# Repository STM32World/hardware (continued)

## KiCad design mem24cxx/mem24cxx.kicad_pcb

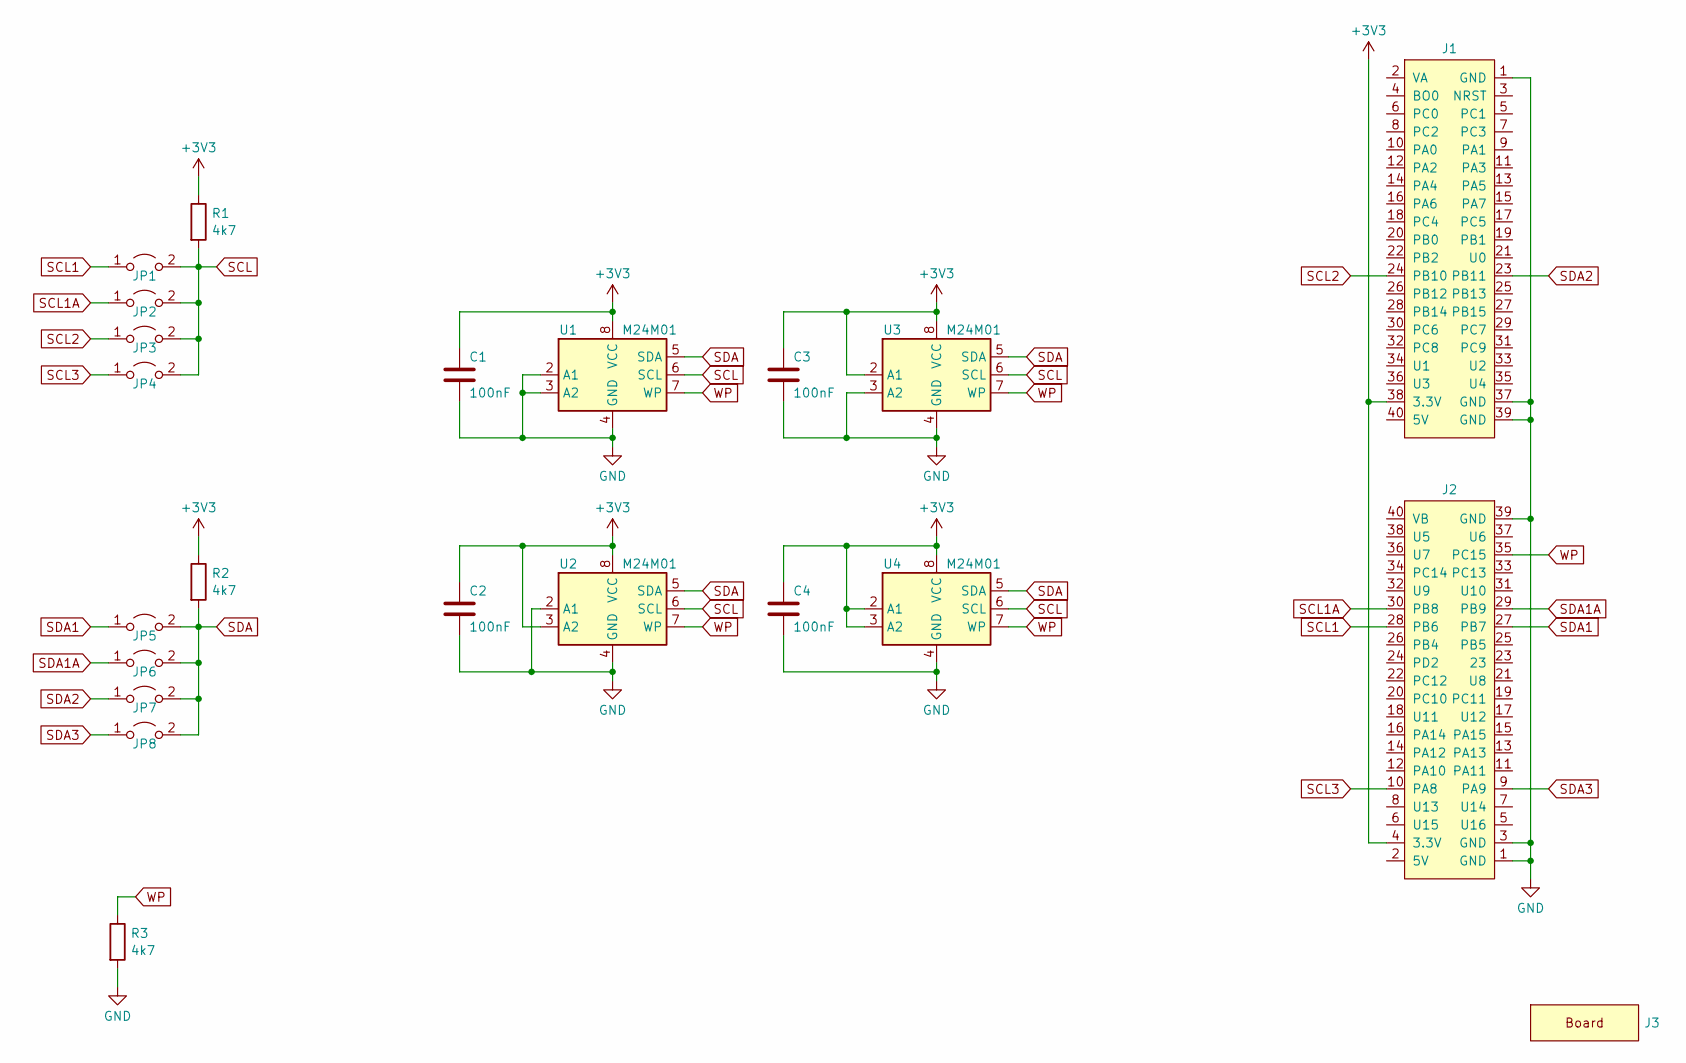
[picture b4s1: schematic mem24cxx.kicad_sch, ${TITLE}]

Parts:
C1, C2, C3, C4: 100nF; C_0603_1608Metric; LCSC C14663
J1: STM32WORLD_CONNECTOR_1; PinSocket_2x20_P2.54mm_Vertical_Stackable; LCSC C35165
J2: STM32WORLD_CONNECTOR_2; PinSocket_2x20_P2.54mm_Vertical_Stackable; LCSC C35165
J3: STM32WORLD_BOARD
JP1, JP2, JP3, JP4, JP5, JP6, JP7, JP8: SolderJumper-2_P1.3mm_Open_TrianglePad1.0x1.5mm
R1, R2, R3: 4k7; R_0603_1608Metric; LCSC C23162
U1, U2, U3, U4: M24M01; SOIC-8_3.9x4.9mm_P1.27mm; LCSC C79990

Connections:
+3V3: C1.1, C2.1, C3.1, C4.1, J1.38 (3.3V), J2.4 (3.3V), R1.1, R2.1, U1.8 (VCC), U2.3 (A2), U2.8 (VCC), U3.2 (A1), U3.8 (VCC), U4.2 (A1), U4.3 (A2), U4.8 (VCC)
GND: C1.2, C2.2, C3.2, C4.2, J1.1 (GND), J1.37 (GND), J1.39 (GND), J2.1 (GND), J2.3 (GND), J2.39 (GND), R3.2, U1.2 (A1), U1.3 (A2), U1.4 (GND), U2.2 (A1), U2.4 (GND), U3.3 (A2), U3.4 (GND), U4.4 (GND)
SCL: JP1.2 (B), JP2.2 (B), JP3.2 (B), JP4.2 (B), R1.2, U1.6 (SCL), U2.6 (SCL), U3.6 (SCL), U4.6 (SCL)
SCL1: J2.28 (PB6), JP1.1 (A)
SCL1A: J2.30 (PB8), JP2.1 (A)
SCL2: J1.24 (PB10), JP3.1 (A)
SCL3: J2.10 (PA8), JP4.1 (A)
SDA: JP5.2 (B), JP6.2 (B), JP7.2 (B), JP8.2 (B), R2.2, U1.5 (SDA), U2.5 (SDA), U3.5 (SDA), U4.5 (SDA)
SDA1: J2.27 (PB7), JP5.1 (A)
SDA1A: J2.29 (PB9), JP6.1 (A)
SDA2: J1.23 (PB11), JP7.1 (A)
SDA3: J2.9 (PA9), JP8.1 (A)
WP: J2.35 (PC15), R3.1, U1.7 (WP), U2.7 (WP), U3.7 (WP), U4.7 (WP)

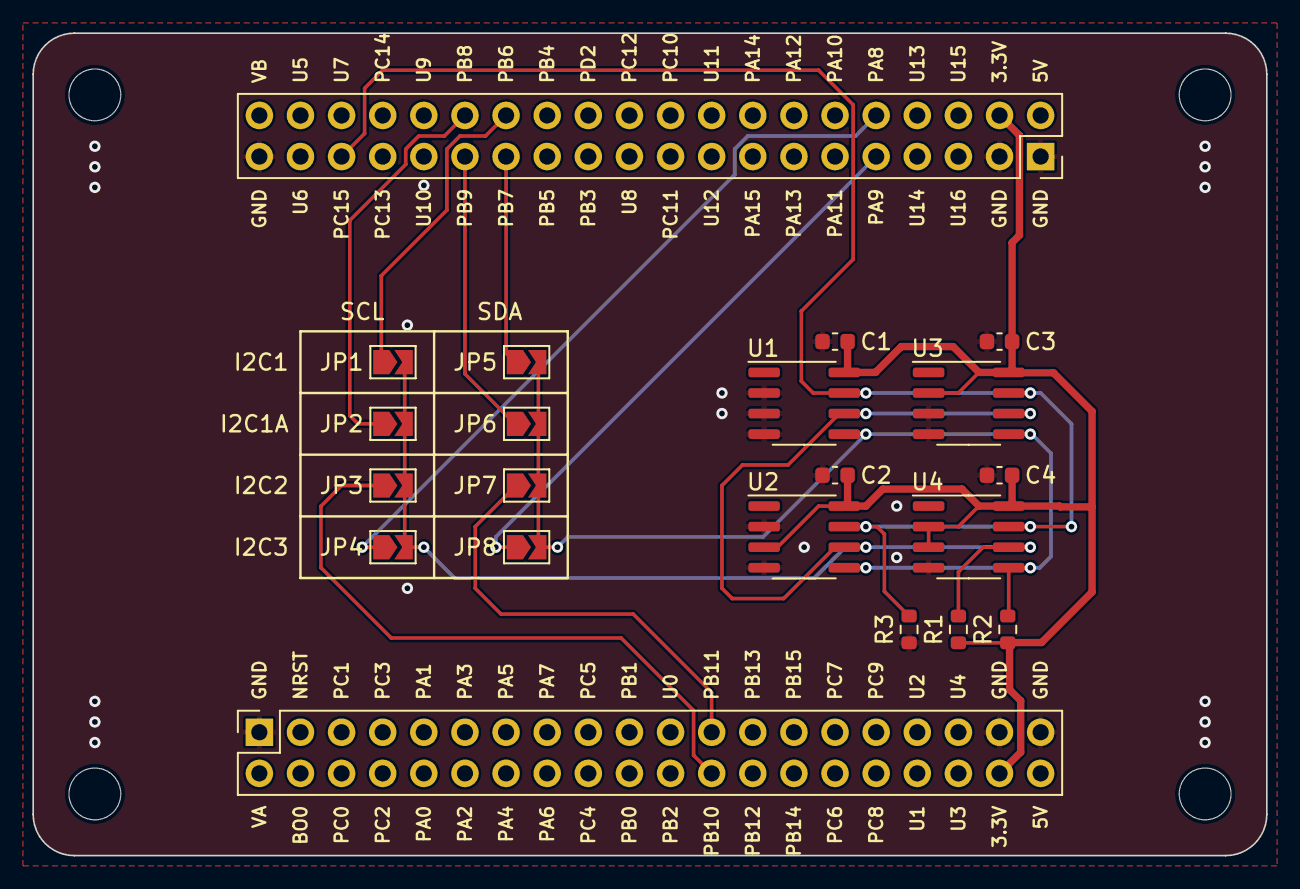
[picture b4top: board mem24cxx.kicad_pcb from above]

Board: 2 copper layers, 76.2 x 50.8 mm, 22 parts (0 on the bottom side), 13 nets.

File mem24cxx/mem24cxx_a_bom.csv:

Comment,Designator,Footprint,LCSC
"100nF","C1,C2,C3,C4","Capacitor_SMD:C_0603_1608Metric","C14663"
"STM32WORLD_CONNECTOR_1","J1","stm32world:PinSocket_2x20_P2.54mm_Vertical_Stackable","C35165"
"STM32WORLD_CONNECTOR_2","J2","stm32world:PinSocket_2x20_P2.54mm_Vertical_Stackable","C35165"
"STM32WORLD_BOARD","J3","stm32world:STM32WORLD_BOARD"
"~","JP1,JP2,JP3,JP4,JP5,JP6,JP7,JP8","Jumper:SolderJumper-2_P1.3mm_Open_TrianglePad1.0x1.5mm"
"4k7","R1,R2,R3","Resistor_SMD:R_0603_1608Metric","C23162"
"M24M01","U1,U2,U3,U4","Package_SO:SOIC-8_3.9x4.9mm_P1.27mm","C79990"

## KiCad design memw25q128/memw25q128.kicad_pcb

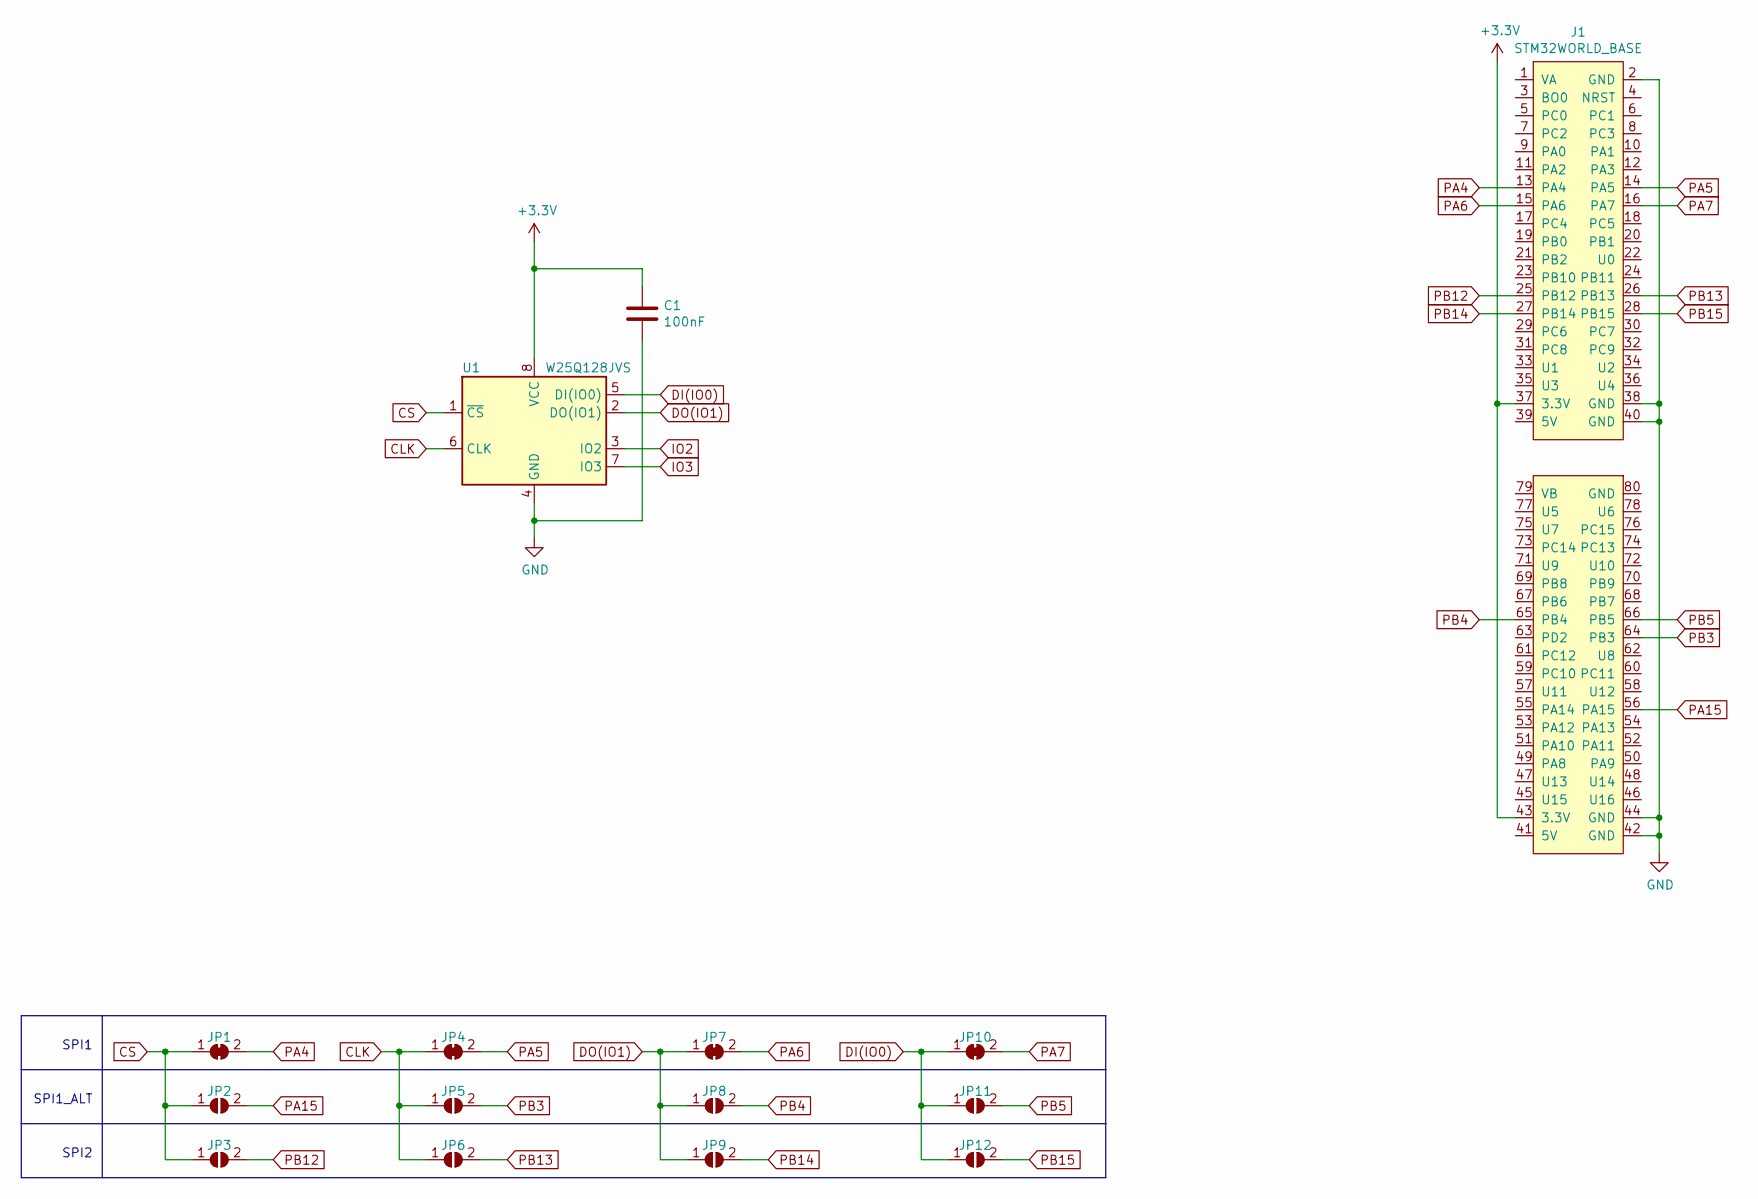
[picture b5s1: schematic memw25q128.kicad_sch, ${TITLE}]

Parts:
C1: C_100NF_0603; C_0603_1608Metric; LCSC C14663
J1: STM32WORLD_BASE
JP1, JP4, JP7, JP10: SolderJumper_2_Bridged; SolderJumper-2_P1.3mm_Bridged_RoundedPad1.0x1.5mm
JP2, JP3, JP5, JP6, JP8, JP9, JP11, JP12: SolderJumper_2_Open; SolderJumper-2_P1.3mm_Open_RoundedPad1.0x1.5mm
U1: W25Q128JVS; SOIC-8_5.275x5.275mm_P1.27mm; LCSC C97521

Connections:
+3V3: C1.1, J1.37 (3.3V), J1.43 (3.3V), U1.8 (VCC)
CLK: JP4.1 (A), JP5.1 (A), JP6.1 (A), U1.6 (CLK)
CS: JP1.1 (A), JP2.1 (A), JP3.1 (A), U1.1 (~CS)
DI(IO0): JP10.1 (A), JP11.1 (A), JP12.1 (A), U1.5 (DI(IO0))
DO(IO1): JP7.1 (A), JP8.1 (A), JP9.1 (A), U1.2 (DO(IO1))
GND: C1.2, J1.2 (GND), J1.38 (GND), J1.40 (GND), J1.42 (GND), J1.44 (GND), U1.4 (GND)
IO2: U1.3 (IO2)
IO3: U1.7 (IO3)
PA4: J1.13 (PA4), JP1.2 (B)
PA5: J1.14 (PA5), JP4.2 (B)
PA6: J1.15 (PA6), JP7.2 (B)
PA7: J1.16 (PA7), JP10.2 (B)
PA15: J1.56 (PA15), JP2.2 (B)
PB3: J1.64 (PB3), JP5.2 (B)
PB4: J1.65 (PB4), JP8.2 (B)
PB5: J1.66 (PB5), JP11.2 (B)
PB12: J1.25 (PB12), JP3.2 (B)
PB13: J1.26 (PB13), JP6.2 (B)
PB14: J1.27 (PB14), JP9.2 (B)
PB15: J1.28 (PB15), JP12.2 (B)

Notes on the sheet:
SPI1_ALT
SPI1
SPI2

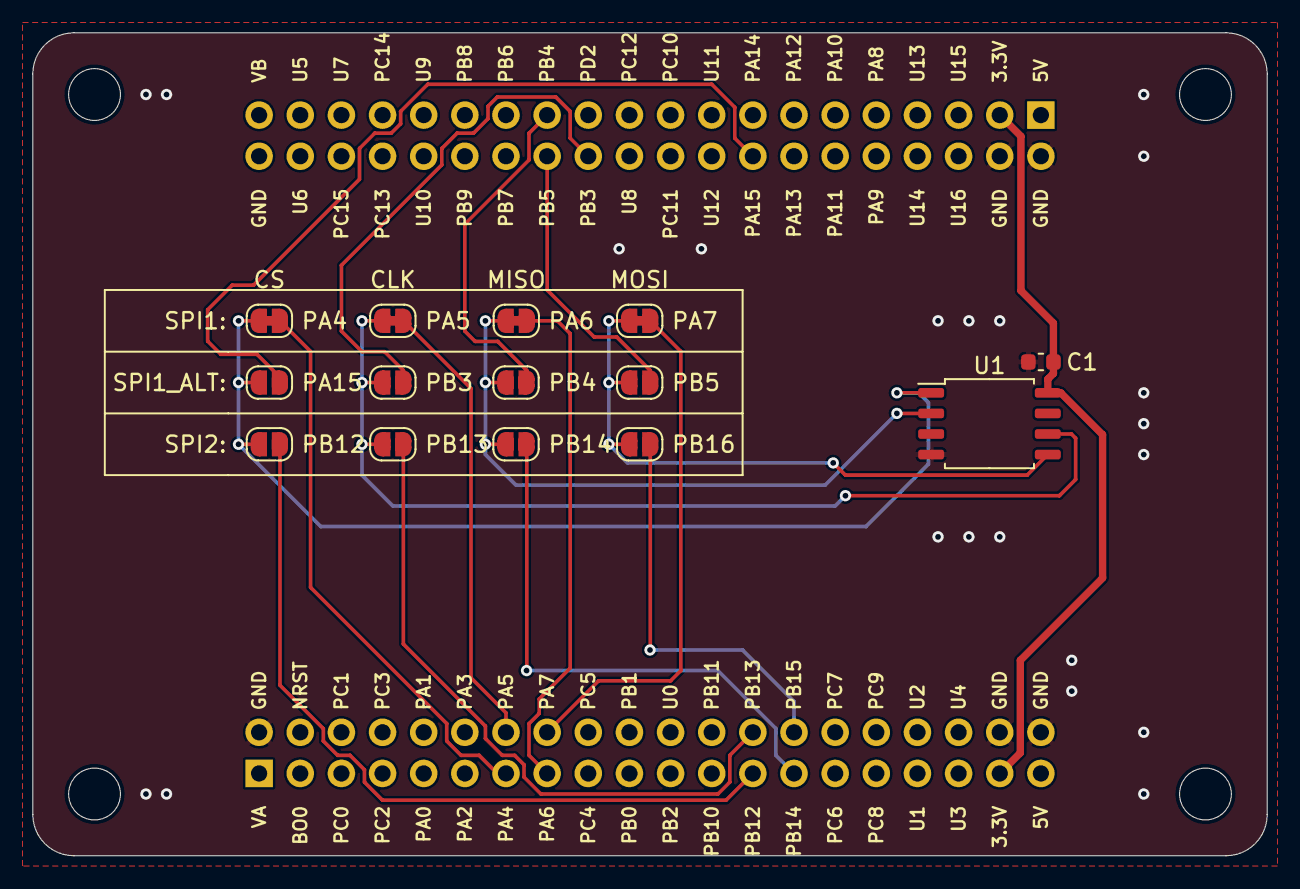
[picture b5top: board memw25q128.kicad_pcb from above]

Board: 2 copper layers, 76.2 x 50.8 mm, 15 parts (0 on the bottom side), 18 nets.

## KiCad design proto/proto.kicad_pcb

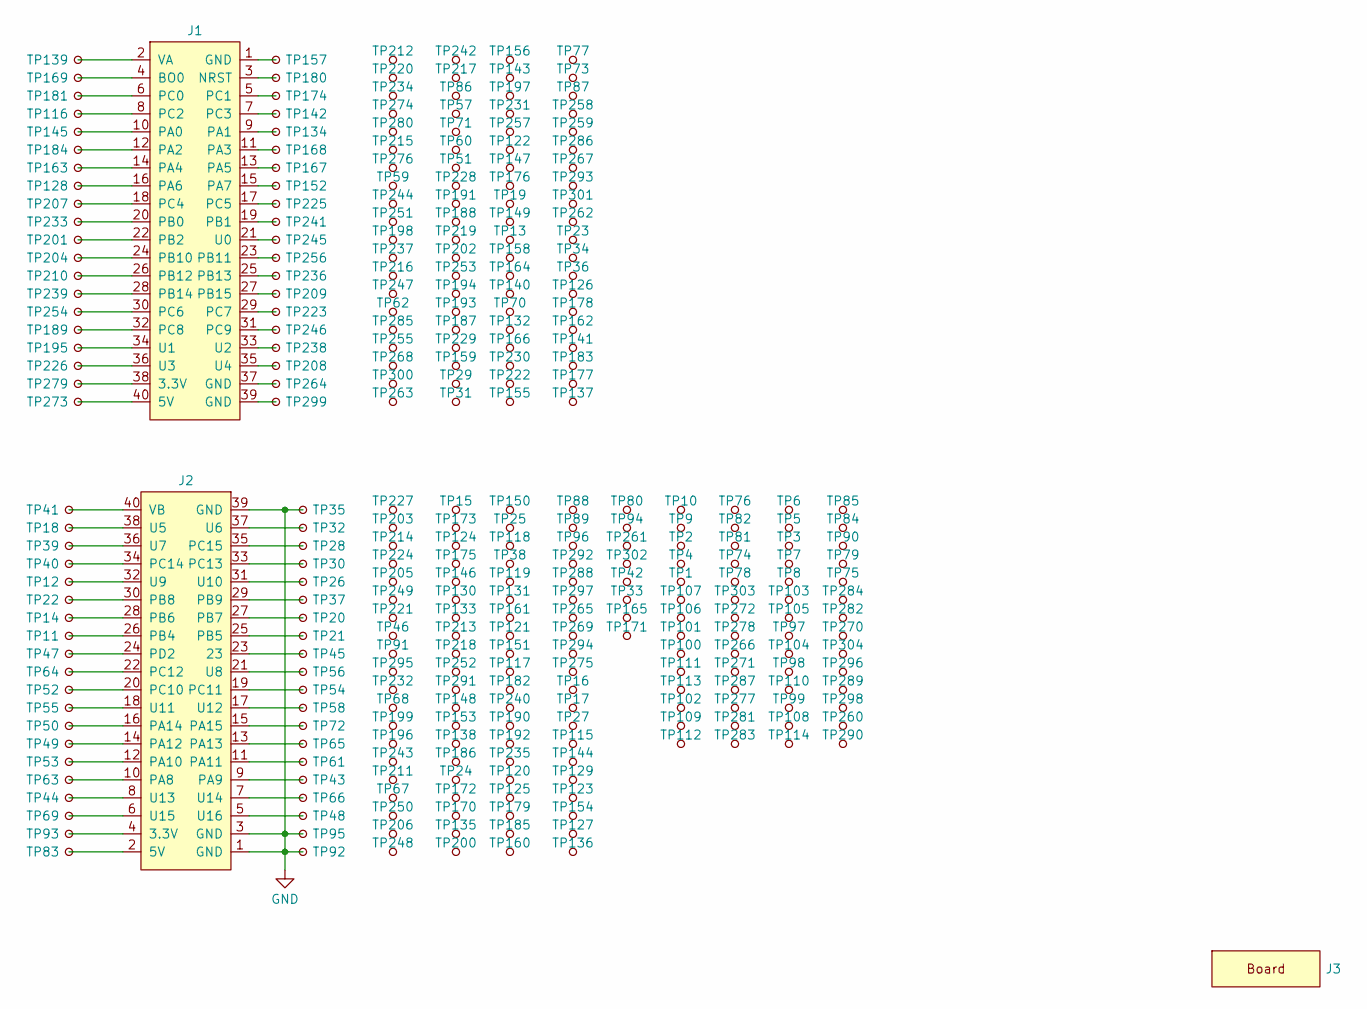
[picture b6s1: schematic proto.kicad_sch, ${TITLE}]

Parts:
J1: STM32WORLD_CONNECTOR_1; PinSocket_2x20_P2.54mm_Vertical_Stackable; LCSC C35165
J2: STM32WORLD_CONNECTOR_2; PinSocket_2x20_P2.54mm_Vertical_Stackable; LCSC C35165
J3: STM32WORLD_BOARD
TP1, TP2, TP3, TP4, TP5, TP6, TP7, TP8, TP9, TP10, TP11, TP12, TP13, TP14, TP15, TP16, TP17, TP18, TP19, TP20, TP21, TP22, TP23, TP24, TP25, TP26, TP27, TP28, TP29, TP30, TP31, TP32, TP33, TP34, TP35, TP36, TP37, TP38, TP39, TP40, TP41, TP42, TP43, TP44, TP45, TP46, TP47, TP48, TP49, TP50, TP51, TP52, TP53, TP54, TP55, TP56, TP57, TP58, TP59, TP60, TP61, TP62, TP63, TP64, TP65, TP66, TP67, TP68, TP69, TP70, TP71, TP72, TP73, TP74, TP75, TP76, TP77, TP78, TP79, TP80, TP81, TP82, TP83, TP84, TP85, TP86, TP87, TP88, TP89, TP90, TP91, TP92, TP93, TP94, TP95, TP96, TP97, TP98, TP99, TP100, TP101, TP102, TP103, TP104, TP105, TP106, TP107, TP108, TP109, TP110, TP111, TP112, TP113, TP114, TP115, TP116, TP117, TP118, TP119, TP120, TP121, TP122, TP123, TP124, TP125, TP126, TP127, TP128, TP129, TP130, TP131, TP132, TP133, TP134, TP135, TP136, TP137, TP138, TP139, TP140, TP141, TP142, TP143, TP144, TP145, TP146, TP147, TP148, TP149, TP150, TP151, TP152, TP153, TP154, TP155, TP156, TP157, TP158, TP159, TP160, TP161, TP162, TP163, TP164, TP165, TP166, TP167, TP168, TP169, TP170, TP171, TP172, TP173, TP174, TP175, TP176, TP177, TP178, TP179, TP180, TP181, TP182, TP183, TP184, TP185, TP186, TP187, TP188, TP189, TP190, TP191, TP192, TP193, TP194, TP195, TP196, TP197, TP198, TP199, TP200, TP201, TP202, TP203, TP204, TP205, TP206, TP207, TP208, TP209, TP210, TP211, TP212, TP213, TP214, TP215, TP216, TP217, TP218, TP219, TP220, TP221, TP222, TP223, TP224, TP225, TP226, TP227, TP228, TP229, TP230, TP231, TP232, TP233, TP234, TP235, TP236, TP237, TP238, TP239, TP240, TP241, TP242, TP243, TP244, TP245, TP246, TP247, TP248, TP249, TP250, TP251, TP252, TP253, TP254, TP255, TP256, TP257, TP258, TP259, TP260, TP261, TP262, TP263, TP264, TP265, TP266, TP267, TP268, TP269, TP270, TP271, TP272, TP273, TP274, TP275, TP276, TP277, TP278, TP279, TP280, TP281, TP282, TP283, TP284, TP285, TP286, TP287, TP288, TP289, TP290, TP291, TP292, TP293, TP294, TP295, TP296, TP297, TP298, TP299, TP300, TP301, TP302, TP303, TP304: TestPoint_Small; PROTO_PAD

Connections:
GND: J2.1 (GND), J2.3 (GND), J2.39 (GND), TP35.1, TP92.1, TP95.1
unnamed: J1.38 (3.3V), TP279.1
unnamed: J1.40 (5V), TP273.1
unnamed: J1.4 (BO0), TP169.1
unnamed: J1.1 (GND), TP157.1
unnamed: J1.37 (GND), TP264.1
unnamed: J1.39 (GND), TP299.1
unnamed: J1.3 (NRST), TP180.1
unnamed: J1.10 (PA0), TP145.1
unnamed: J1.9 (PA1), TP134.1
unnamed: J1.12 (PA2), TP184.1
unnamed: J1.11 (PA3), TP168.1
unnamed: J1.14 (PA4), TP163.1
unnamed: J1.13 (PA5), TP167.1
unnamed: J1.16 (PA6), TP128.1
unnamed: J1.15 (PA7), TP152.1
unnamed: J1.20 (PB0), TP233.1
unnamed: J1.19 (PB1), TP241.1
unnamed: J1.22 (PB2), TP201.1
unnamed: J1.24 (PB10), TP204.1
unnamed: J1.23 (PB11), TP256.1
unnamed: J1.26 (PB12), TP210.1
unnamed: J1.25 (PB13), TP236.1
unnamed: J1.28 (PB14), TP239.1
unnamed: J1.27 (PB15), TP209.1
unnamed: J1.6 (PC0), TP181.1
unnamed: J1.5 (PC1), TP174.1
unnamed: J1.8 (PC2), TP116.1
unnamed: J1.7 (PC3), TP142.1
unnamed: J1.18 (PC4), TP207.1
unnamed: J1.17 (PC5), TP225.1
unnamed: J1.30 (PC6), TP254.1
unnamed: J1.29 (PC7), TP223.1
unnamed: J1.32 (PC8), TP189.1
unnamed: J1.31 (PC9), TP246.1
unnamed: J1.21 (U0), TP245.1
unnamed: J1.34 (U1), TP195.1
unnamed: J1.33 (U2), TP238.1
unnamed: J1.36 (U3), TP226.1
unnamed: J1.35 (U4), TP208.1
unnamed: J1.2 (VA), TP139.1
unnamed: J2.4 (3.3V), TP93.1
unnamed: J2.2 (5V), TP83.1
unnamed: J2.10 (PA8), TP63.1
unnamed: J2.9 (PA9), TP43.1
unnamed: J2.12 (PA10), TP53.1
unnamed: J2.11 (PA11), TP61.1
unnamed: J2.14 (PA12), TP49.1
unnamed: J2.13 (PA13), TP65.1
unnamed: J2.16 (PA14), TP50.1
unnamed: J2.15 (PA15), TP72.1
unnamed: J2.26 (PB4), TP11.1
unnamed: J2.25 (PB5), TP21.1
unnamed: J2.28 (PB6), TP14.1
unnamed: J2.27 (PB7), TP20.1
unnamed: J2.30 (PB8), TP22.1
unnamed: J2.29 (PB9), TP37.1
unnamed: J2.20 (PC10), TP52.1
unnamed: J2.19 (PC11), TP54.1
unnamed: J2.22 (PC12), TP64.1
unnamed: J2.33 (PC13), TP30.1
unnamed: J2.34 (PC14), TP40.1
unnamed: J2.35 (PC15), TP28.1
unnamed: J2.24 (PD2), TP47.1
unnamed: J2.23, TP45.1
unnamed: J2.38 (U5), TP18.1
unnamed: J2.37 (U6), TP32.1
unnamed: J2.36 (U7), TP39.1
unnamed: J2.21 (U8), TP56.1
unnamed: J2.32 (U9), TP12.1
unnamed: J2.31 (U10), TP26.1
unnamed: J2.18 (U11), TP55.1
unnamed: J2.17 (U12), TP58.1
unnamed: J2.8 (U13), TP44.1
unnamed: J2.7 (U14), TP66.1
unnamed: J2.6 (U15), TP69.1
unnamed: J2.5 (U16), TP48.1
unnamed: J2.40 (VB), TP41.1

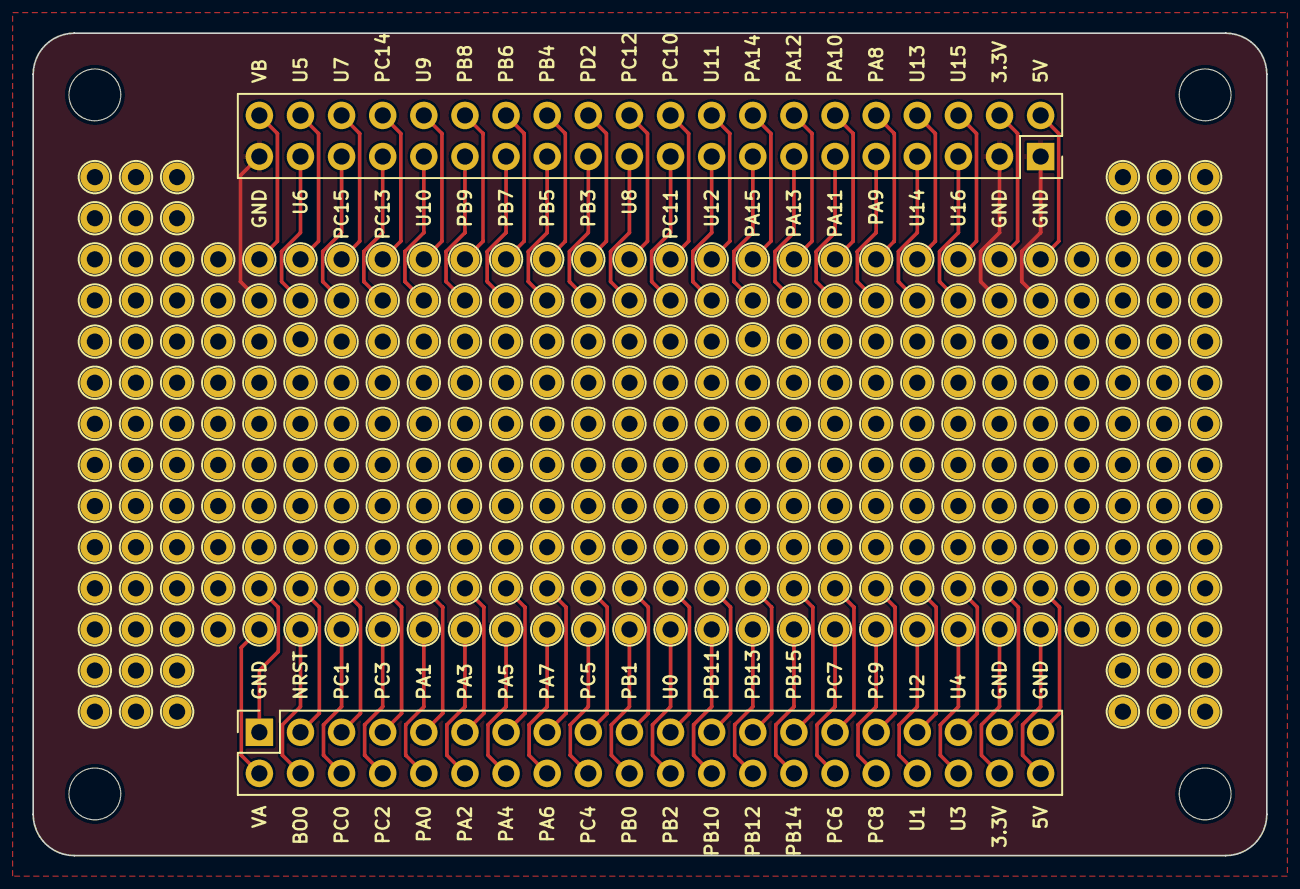
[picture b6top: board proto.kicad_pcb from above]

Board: 2 copper layers, 76.2 x 50.8 mm, 307 parts (0 on the bottom side), 78 nets.

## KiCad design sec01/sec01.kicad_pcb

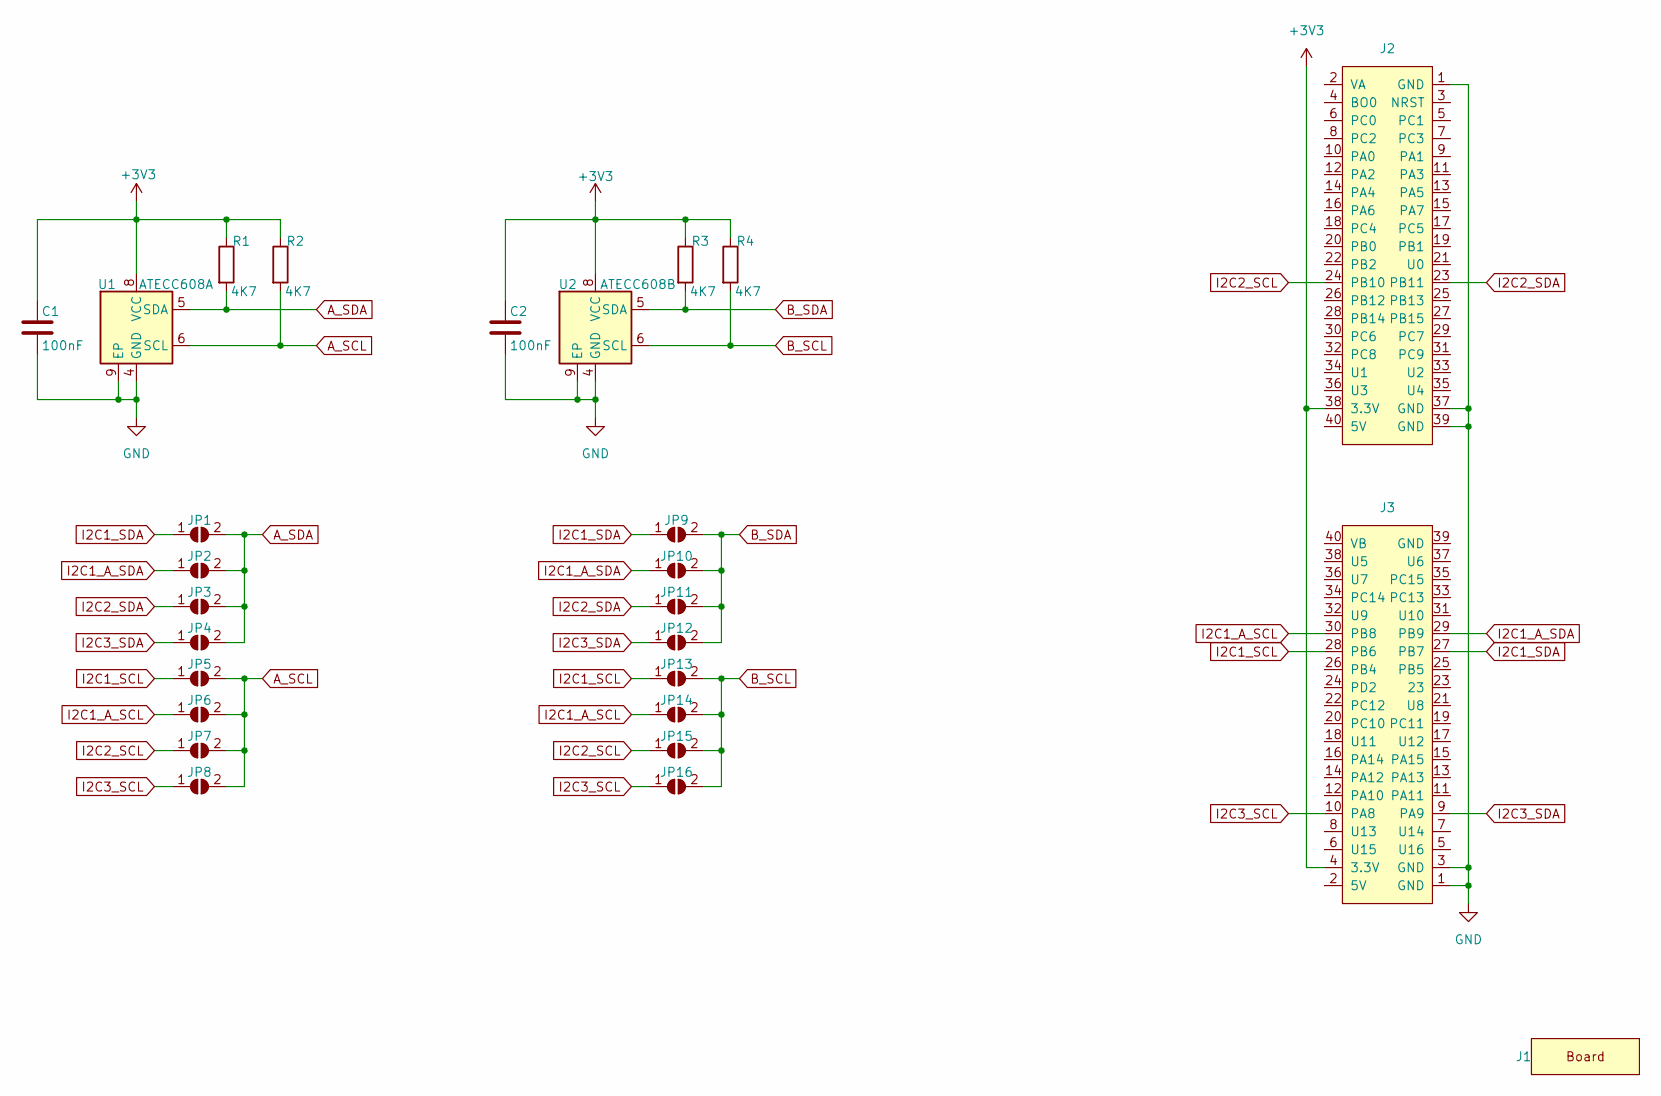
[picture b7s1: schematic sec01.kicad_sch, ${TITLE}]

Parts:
C1, C2: 100nF; C_0603_1608Metric; LCSC C14663
J1: STM32WORLD_BOARD
J2: STM32WORLD_CONNECTOR_1; PinSocket_2x20_P2.54mm_Vertical_Stackable; LCSC C35165
J3: STM32WORLD_CONNECTOR_2; PinSocket_2x20_P2.54mm_Vertical_Stackable; LCSC C35165
JP1, JP2, JP3, JP4, JP5, JP6, JP7, JP8, JP9, JP10, JP11, JP12, JP13, JP14, JP15, JP16: SolderJumper_2_Open; SolderJumper-2_P1.3mm_Open_RoundedPad1.0x1.5mm
R1, R2, R3, R4: 4K7; R_0603_1608Metric; LCSC C23162
U1: ATECC608A; DFN-8-1EP_3x2mm_P0.5mm_EP1.3x1.5mm; LCSC C616908
U2: ATECC608B; DFN-8-1EP_3x2mm_P0.5mm_EP1.3x1.5mm; LCSC C17350254

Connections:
+3V3: C1.1, C2.1, J2.38 (3.3V), J3.4 (3.3V), R1.1, R2.1, R3.1, R4.1, U1.8 (VCC), U2.8 (VCC)
A_SCL: JP5.2 (B), JP6.2 (B), JP7.2 (B), JP8.2 (B), R2.2, U1.6 (SCL)
A_SDA: JP1.2 (B), JP2.2 (B), JP3.2 (B), JP4.2 (B), R1.2, U1.5 (SDA)
B_SCL: JP13.2 (B), JP14.2 (B), JP15.2 (B), JP16.2 (B), R4.2, U2.6 (SCL)
B_SDA: JP9.2 (B), JP10.2 (B), JP11.2 (B), JP12.2 (B), R3.2, U2.5 (SDA)
GND: C1.2, C2.2, J2.1 (GND), J2.37 (GND), J2.39 (GND), J3.1 (GND), J3.3 (GND), U1.4 (GND), U1.9 (EP), U2.4 (GND), U2.9 (EP)
I2C1_A_SCL: J3.30 (PB8), JP6.1 (A), JP14.1 (A)
I2C1_A_SDA: J3.29 (PB9), JP2.1 (A), JP10.1 (A)
I2C1_SCL: J3.28 (PB6), JP5.1 (A), JP13.1 (A)
I2C1_SDA: J3.27 (PB7), JP1.1 (A), JP9.1 (A)
I2C2_SCL: J2.24 (PB10), JP7.1 (A), JP15.1 (A)
I2C2_SDA: J2.23 (PB11), JP3.1 (A), JP11.1 (A)
I2C3_SCL: J3.10 (PA8), JP8.1 (A), JP16.1 (A)
I2C3_SDA: J3.9 (PA9), JP4.1 (A), JP12.1 (A)

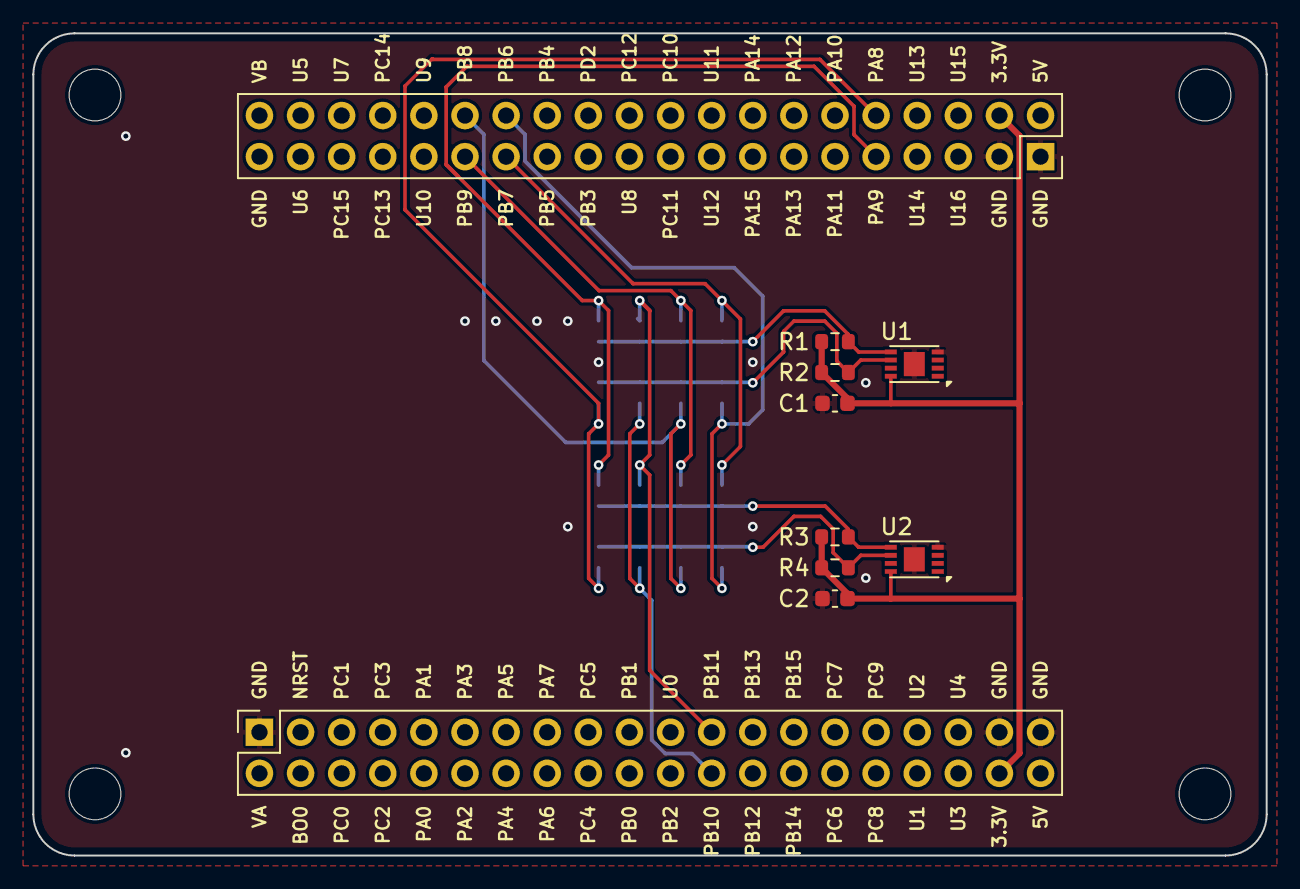
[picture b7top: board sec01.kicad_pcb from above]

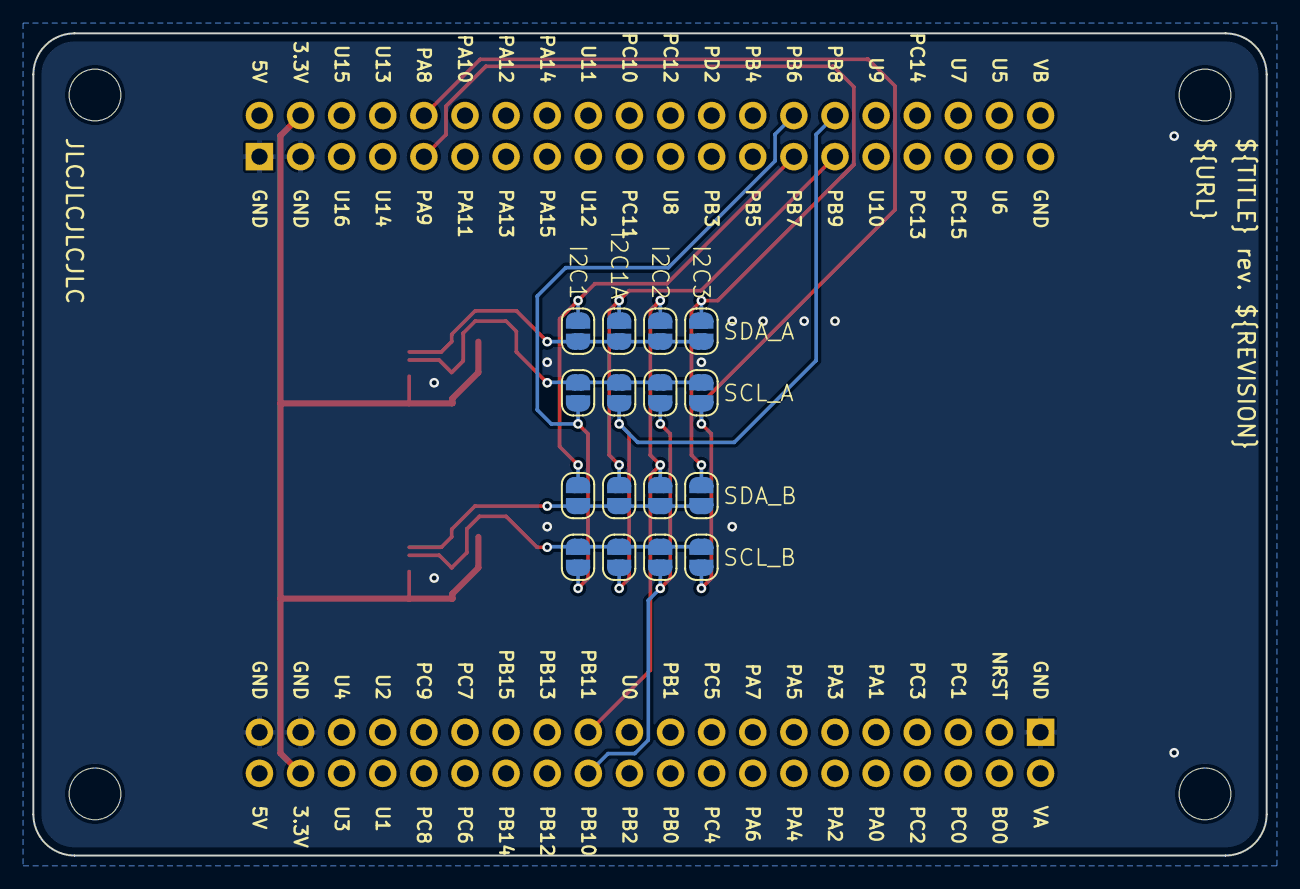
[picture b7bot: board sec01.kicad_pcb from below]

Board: 2 copper layers, 76.2 x 50.8 mm, 27 parts (16 on the bottom side), 14 nets.

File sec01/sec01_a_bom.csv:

"1","2","C1, C2","100nF","Device:C","Capacitor_SMD:C_0603_1608Metric","~","","~","Unpolarized capacitor","Capacitor_SMD:C_0603_1608Metric","C14663"
"2","1","J1","STM32WORLD_BOARD","stm32world:STM32WORLD_BOARD","stm32world:STM32WORLD_BOARD","","","","","stm32world:STM32WORLD_BOARD",""
"3","1","J2","STM32WORLD_CONNECTOR_1","stm32world:STM32WORLD_CONNECTOR_1","stm32world:PinSocket_2x20_P2.54mm_Vertical_Stackable","","","","","stm32world:PinSocket_2x20_P2.54mm_Vertical_Stackable","C35165"
"4","1","J3","STM32WORLD_CONNECTOR_2","stm32world:STM32WORLD_CONNECTOR_2","stm32world:PinSocket_2x20_P2.54mm_Vertical_Stackable","","","","","stm32world:PinSocket_2x20_P2.54mm_Vertical_Stackable","C35165"
"5","16","JP1, JP2, JP3, JP4, JP5, JP6, JP7, JP8, JP9, JP10, JP11, JP12, JP13, JP14, JP15, JP16","SolderJumper_2_Open","stm32world:SolderJumper_2_Open","Jumper:SolderJumper-2_P1.3mm_Open_RoundedPad1.0x1.5mm","~","","~","Solder Jumper, 2-pole, open","Jumper:SolderJumper-2_P1.3mm_Open_RoundedPad1.0x1.5mm",""
"6","4","R1, R2, R3, R4","4K7","Device:R","Resistor_SMD:R_0603_1608Metric","~","","~","Resistor","Resistor_SMD:R_0603_1608Metric","C23162"
"7","1","U1","ATECC608A","Security:ATECC608A-MAHDA","Package_DFN_QFN:DFN-8-1EP_3x2mm_P0.5mm_EP1.3x1.5mm","http://ww1.microchip.com/downloads/en/DeviceDoc/ATECC608A-Cr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","","http://ww1.microchip.com/downloads/en/DeviceDoc/ATECC608A-Cr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","Cryptographic Co-Processor with Secure Hardware-based 16 Key Storage, ECDSA and ECDH support, I2C, UDFN-8","Package_DFN_QFN:DFN-8-1EP_3x2mm_P0.5mm_EP1.3x1.5mm","C616908"
"8","1","U2","ATECC608B","Security:ATECC608B-MAHDA","Package_DFN_QFN:DFN-8-1EP_3x2mm_P0.5mm_EP1.3x1.5mm","https://ww1.microchip.com/downloads/aemDocuments/documents/S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","","https://ww1.microchip.com/downloads/aemDocuments/documents/S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","Cryptographic Co-Processor with Secure Hardware-based 16 Key Storage, ECDSA and ECDH support, I2C, UDFN-8","Package_DFN_QFN:DFN-8-1EP_3x2mm_P0.5mm_EP1.3x1.5mm","C17350254"
